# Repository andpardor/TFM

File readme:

para ejecutar los gateways y el programa de alarmas:

python nombre_del_programa.py nombre_carperta_archivos_conf

archivo acl: lista de dispositvos permitidos
archivo gw: configuración puertos y accesos del gateway y mqtt

Las carpetas.X son los fuentes de los pic que se deben utilizar en el programa MPLAB X de microchip

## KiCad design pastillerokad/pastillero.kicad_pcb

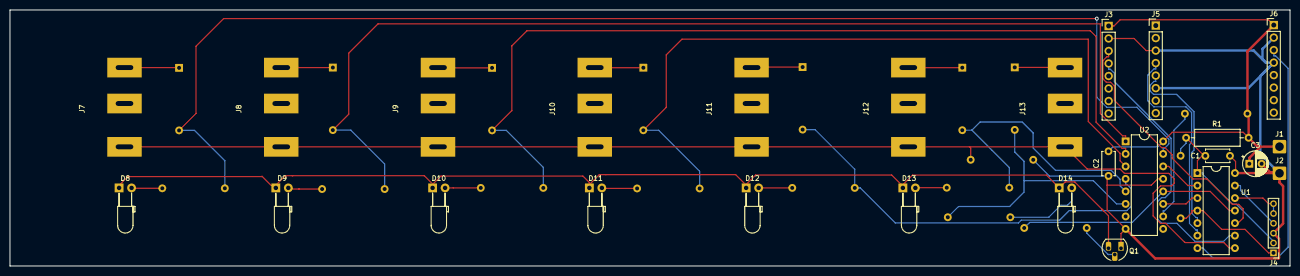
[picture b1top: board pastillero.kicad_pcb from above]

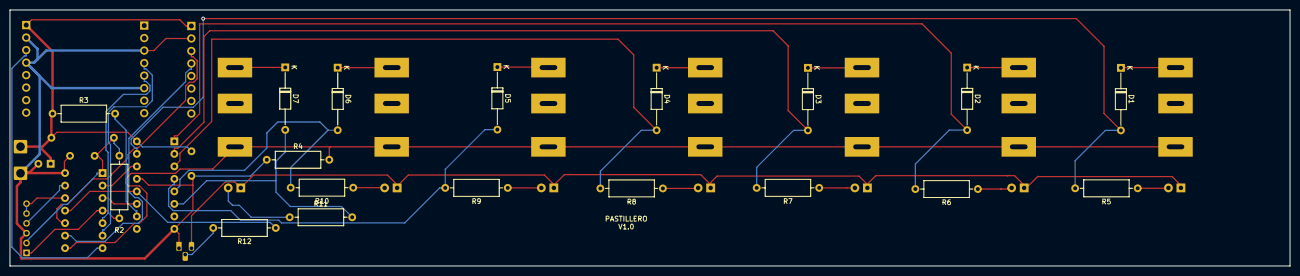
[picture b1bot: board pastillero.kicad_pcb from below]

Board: 2 copper layers, 260.0 x 52.0 mm, 45 parts (18 on the bottom side), 39 nets.

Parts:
C1, C2: 100nF; C_Disc_D4.7mm_W2.5mm_P5.00mm
C3: 4.7uF; CP_Radial_D5.0mm_P2.50mm
D1, D2, D3, D4, D5, D6, D7: BAT42; D_DO-35_SOD27_P12.70mm_Horizontal
D8, D9, D10, D11, D12, D13, D14: LED; LED_D3.0mm_Horizontal_O3.81mm_Z2.0mm
J1, J2: Conn_01x01; SolderWire-1sqmm_1x01_D1.4mm_OD2.7mm
J3, J5, J6: Conn_01x08; PinHeader_1x08_P2.54mm_Vertical
J4: Conn_01x06; PinHeader_1x06_P2.00mm_Vertical
J7, J8, J9, J10, J11, J12, J13: FCAR; m_limit_switch
Q1: PN2222; TO-92L_HandSolder
R1: 0R; R_Axial_DIN0309_L9.0mm_D3.2mm_P12.70mm_Horizontal
R2: 10K; R_Axial_DIN0309_L9.0mm_D3.2mm_P12.70mm_Horizontal
R3, R4, R12: 4K7; R_Axial_DIN0309_L9.0mm_D3.2mm_P12.70mm_Horizontal
R5, R6, R7, R8, R9, R11: 470R; R_Axial_DIN0309_L9.0mm_D3.2mm_P12.70mm_Horizontal
R10: R_US; R_Axial_DIN0309_L9.0mm_D3.2mm_P12.70mm_Horizontal
U1: PIC16F18326-I_JQ; DIP-14_W7.62mm
U2: 74HC595; DIP-16_W7.62mm

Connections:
GND: C1.1, C2.1, C3.2, J2.1, J3.2, J4.3, J5.3, J5.6, J6.2, J6.4, Q1.1, R4.1, U1.14, U2.8, U2.13
MCLR: J4.1, R2.2, U1.4
unnamed: C1.2, J4.2, R1.2, R2.1, U1.1
unnamed: D1.1, J7.3
unnamed: D1.2, R5.2, U2.15
unnamed: D2.1, J8.3
unnamed: D2.2, R6.2, U2.1
unnamed: D3.1, J9.3
unnamed: D3.2, R7.2, U2.2
unnamed: D4.1, J10.3
unnamed: D4.2, R8.2, U2.3
unnamed: D5.1, J11.3
unnamed: D5.2, R9.2, U2.4
unnamed: D6.1, J12.3
unnamed: D6.2, R10.2, U2.5
unnamed: D7.1, J13.3
unnamed: D7.2, R11.2, U2.6
unnamed: D8.2, R5.1
unnamed: D9.2, R6.1
unnamed: D8.1, D9.1, D10.1, D11.1, D12.1, D13.1, D14.1, Q1.3
unnamed: D10.2, R7.1
unnamed: D11.2, R8.1
unnamed: D12.2, R9.1
unnamed: D13.2, R10.1
unnamed: D14.2, R11.1
unnamed: J7.1, J8.1, J9.1, J10.1, J11.1, J12.1, J13.1, R4.2, U1.8
unnamed: Q1.2, R12.2
unnamed: R3.2, U2.10
PGEC: J4.5, J4.6, U1.12
PGED: J4.4, U1.13
PWX: J6.3, U1.7
RCLK: R12.1, U1.11, U2.12
RXD: J5.4, U1.6
SCL: J3.3, U1.10
SDA: J3.4, U1.9
SER: U1.2, U2.14
SER_CLK: U1.3, U2.11
TXD: J5.5, U1.5
VBAT: C2.2, C3.1, J1.1, J3.1, J6.1, R1.1, R3.1, U2.16

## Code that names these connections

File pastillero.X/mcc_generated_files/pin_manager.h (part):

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// get/set RCLK aliases
#define RCLK_TRIS                 TRISAbits.TRISA2
#define RCLK_LAT                  LATAbits.LATA2
#define RCLK_PORT                 PORTAbits.RA2
#define RCLK_WPU                  WPUAbits.WPUA2
#define RCLK_OD                   ODCONAbits.ODCA2
#define RCLK_ANS                  ANSELAbits.ANSA2
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// get/set SER_CLK aliases
#define SER_CLK_TRIS                 TRISAbits.TRISA4
#define SER_CLK_LAT                  LATAbits.LATA4
#define SER_CLK_PORT                 PORTAbits.RA4
#define SER_CLK_WPU                  WPUAbits.WPUA4
#define SER_CLK_OD                   ODCONAbits.ODCA4
#define SER_CLK_ANS                  ANSELAbits.ANSA4
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// get/set SER aliases
#define SER_TRIS                 TRISAbits.TRISA5
#define SER_LAT                  LATAbits.LATA5
#define SER_PORT                 PORTAbits.RA5
#define SER_WPU                  WPUAbits.WPUA5
#define SER_OD                   ODCONAbits.ODCA5
#define SER_ANS                  ANSELAbits.ANSA5
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// get/set PWX aliases
#define PWX_TRIS                 TRISCbits.TRISC3
#define PWX_LAT                  LATCbits.LATC3
#define PWX_PORT                 PORTCbits.RC3
#define PWX_WPU                  WPUCbits.WPUC3
#define PWX_OD                   ODCONCbits.ODCC3
#define PWX_ANS                  ANSELCbits.ANSC3
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
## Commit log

2021-08-11 Version inicial
2021-08-12 version1.1
2021-08-12 version1.2
2021-08-14 nueva interfaz mpu6050 para manejar fifo y muestreo a 4 Hz. velocidad CPU 12 Mhz. Velocidad I2c 400Khz. Nuevo pin para TX_GPS para control de sleep.
2021-08-14 añado eeprom funciones para configuracion en eeprom funciones adicionales gsm para voz y configuracion desde eerprom gps comandos de sleep
2021-08-15 modifico estructura de trama funciones de alto nivel acelerometro
2021-08-16 primera version completa cambios en la trama de comunicacion calculo del modulo del vector sin raiz cuadrada
2021-08-18 se hace close pero no shutdown al cerrar la comunicacion, en cambio se hace start en arranque por si acaso se ha cerrado. tratamiento cerrojo de llamada de voz apagado de gps con envio de caracter es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
2021-08-19 Add files via upload
    Gateway del collar y de la caja de medicinas
2021-08-19 Ajuste de flags. comentarios y cabeceras. Arranque en caliente.
2021-09-16 Version final
2021-09-16 anhadido pastillero

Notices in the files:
pastillero.X/mcc_generated_files/pin_manager.h:
(c) 2018 Microchip Technology Inc. and its subsidiaries.
